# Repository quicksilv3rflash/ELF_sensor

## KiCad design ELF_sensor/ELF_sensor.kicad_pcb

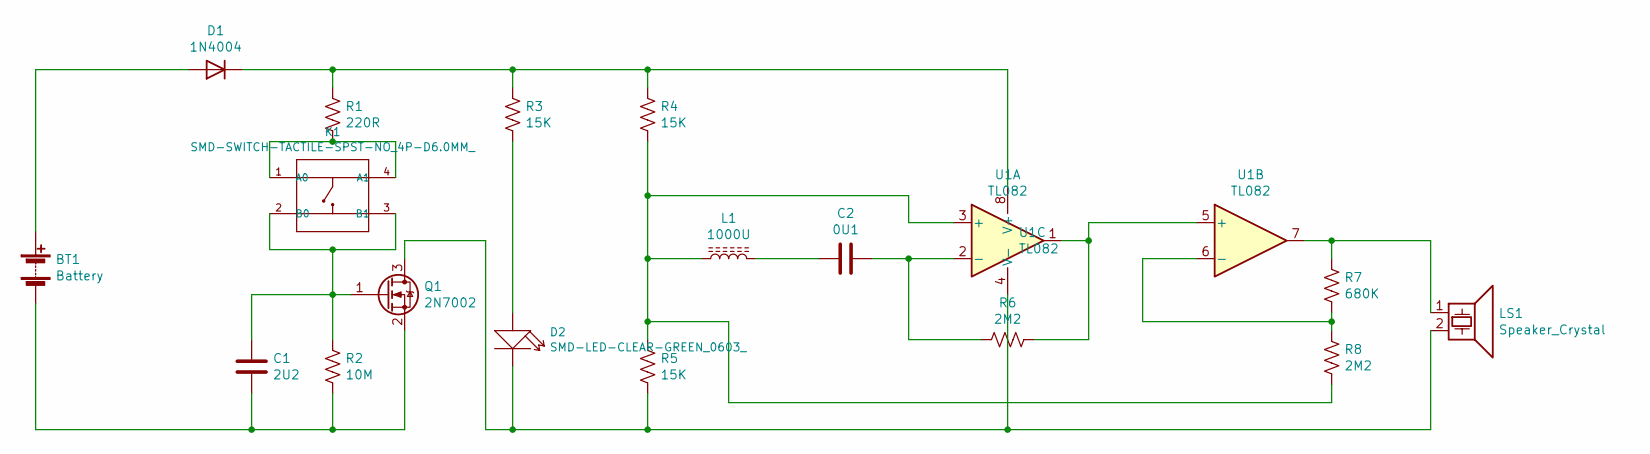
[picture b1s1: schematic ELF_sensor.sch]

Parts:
BT1: Battery; PinSocket_1x02_P2.54mm_Vertical
C1: 2U2; C1206
C2: 0U1; C0603
D1: 1N4004; D_SOD-123F
D2: SMD-LED-CLEAR-GREEN_0603_; LED-0603; MPN 19-217-G7C-AN1P2-3T
K1: SMD-SWITCH-TACTILE-SPST-NO_4P-D6.0MM_; DTSM-62K-S-V-T_R_SN431; MPN DTSM-62K-S-V-T_R_SN431_
L1: 1000U; L_Radial_D7.5mm_P2.5mm
LS1: Speaker_Crystal; HNR-2310A
Q1: 2N7002; SOT-23
R1: 220R; R0603
R2: 10M; R0603
R3, R4, R5: 15K; R0603
R6, R8: 2M2; R0603
R7: 680K; R0603
U1: TL082; SOIC8-1.27-5X4MM

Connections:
unnamed: BT1.1 (+), D1.2 (A)
unnamed: BT1.2 (-), C1.2, Q1.2 (S), R2.2
unnamed: C1.1, K1.2 (B0), K1.3 (B1), Q1.1 (G), R2.1
unnamed: C2.1, R6.2, U1.2 (-)
unnamed: C2.2, L1.2
unnamed: D1.1 (K), R1.1, R3.1, R4.1, U1.8 (V+)
unnamed: D2.1 (+), R3.2
unnamed: D2.2 (-), LS1.2, Q1.3 (D), R5.2, U1.4 (V-)
unnamed: K1.1 (A0), K1.4 (A1), R1.2
unnamed: L1.1, R4.2, R5.1, R8.2, U1.3 (+)
unnamed: LS1.1, R7.1, U1.7
unnamed: R6.1, U1.1, U1.5 (+)
unnamed: R7.2, R8.1, U1.6 (-)

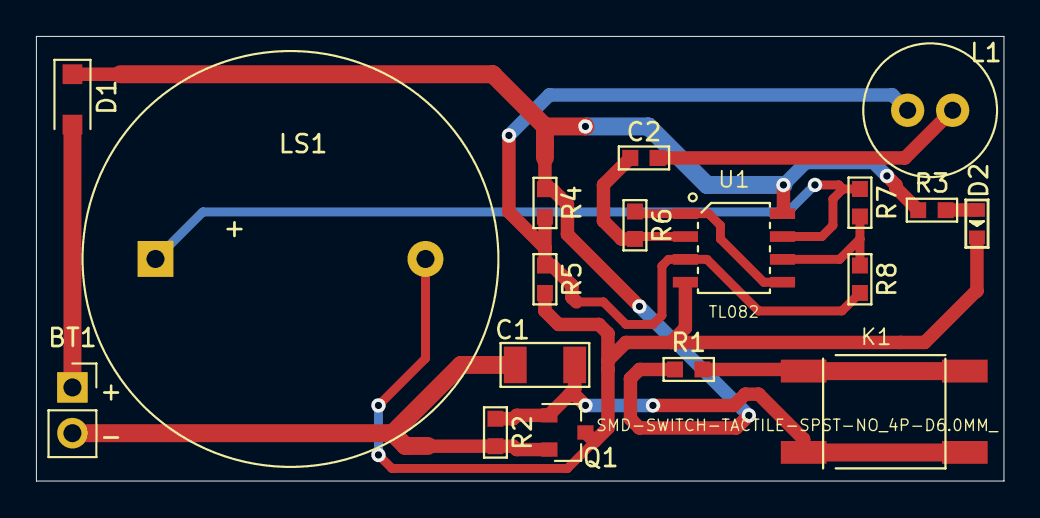
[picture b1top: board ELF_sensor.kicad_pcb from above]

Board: 2 copper layers, 53.8 x 24.7 mm, 18 parts (0 on the bottom side), 13 nets.

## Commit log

2026-04-09 Uploaded project files
2026-04-09 Added Instructables writeup
2026-06-09 Create LICENSE.md
    Creative Commons Zero V1.0 Universal
